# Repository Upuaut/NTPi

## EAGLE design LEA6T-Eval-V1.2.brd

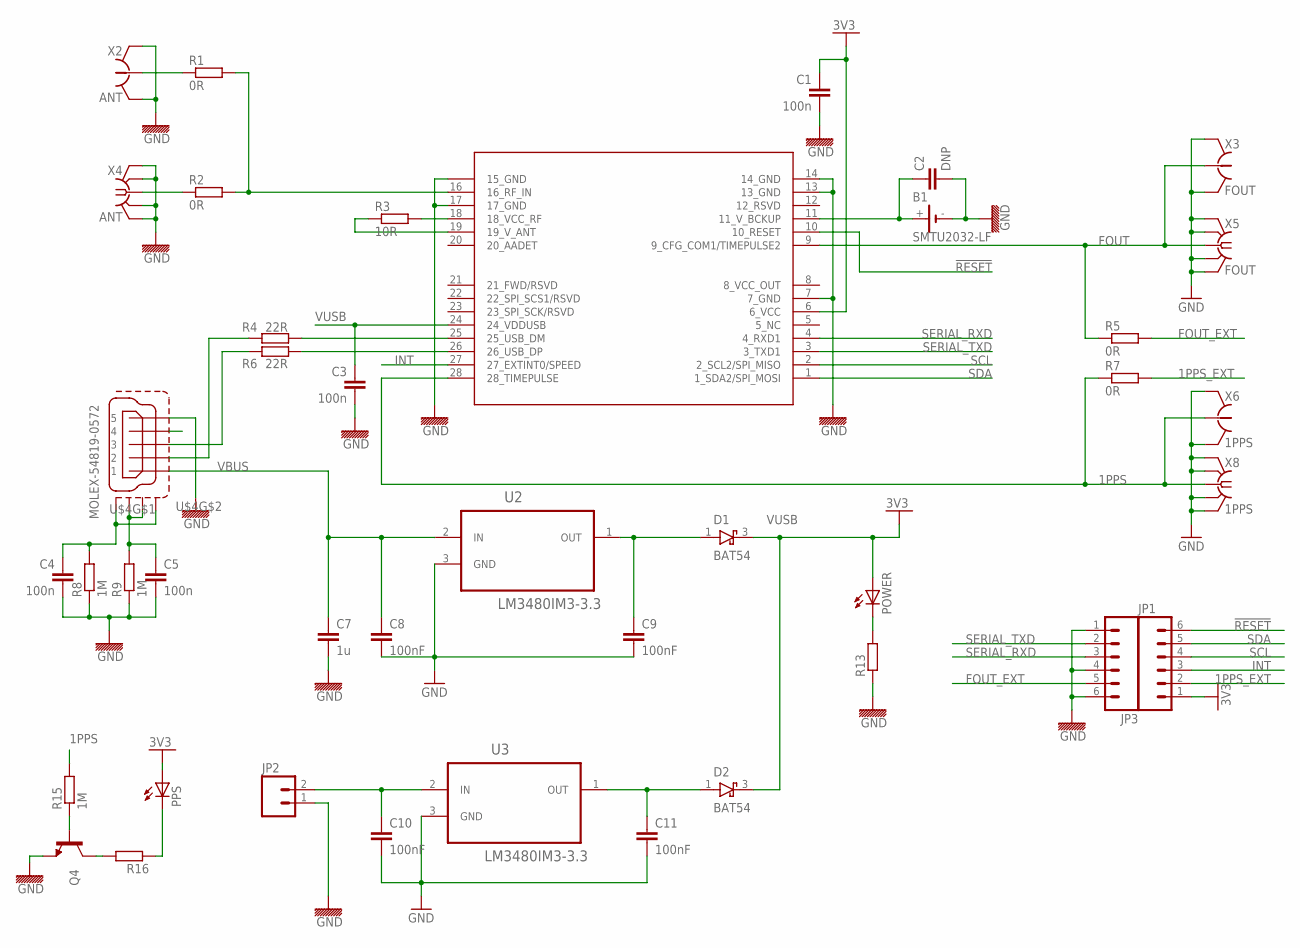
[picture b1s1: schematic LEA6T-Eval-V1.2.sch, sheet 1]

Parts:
B1: SMTU2032-LF; SMTU2032
C1, C3, C4, C5: 100n; 0603
C2: DNP; 0603
C7: 1u; 0603
C8, C9, C10, C11: 100nF; 0603-CAP
D1, D2: BAT54; SOT23
JP1, JP3: M06SIP; 1X06
JP2: M02PTH; 1X02
POWER: LEDSML0603; SML0603
PPS: LEDSML0603; SML0603
Q4: TRANSISTOR_NPNSOT23; SOT23
R1, R2, R5, R7: 0R; 0603
R3: 10R; 0603
R4, R6: 22R; 0603
R8, R9, R15: 1M; 0603
R13, R16: R-EU_0603; 0603
U1: UBLOX_LEA-6; UBLOX_LEA-6T
U2, U3: LM3480IM3-3.3; SOT95P251X112-3N
U$4: MOLEX-54819-0572
X2: ANT; HRS_UFL
X3: FOUT; HRS_UFL
X4: ANT; SMA-F-S-EDGE
X5: FOUT; SMA-F-S-EDGE
X6: 1PPS; HRS_UFL
X8: 1PPS; SMA-F-S-EDGE

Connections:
1PPS: R7.1, R15.2, U1.28 (28_TIMEPULSE), X6.SIG (1), X8.C (1)
1PPS_EXT: JP1.2, R7.2; also elsewhere on the board
3V3: C1.1, D1.3 (C), D2.3 (C), JP1.1, POWER.A, PPS.A, U1.6 (6_VCC); also elsewhere on the board
!RESET: JP1.6, U1.10 (10_RESET)
FOUT: R5.1, U1.9 (9_CFG_COM1/TIMEPULSE2), X3.SIG (1), X5.C (1)
FOUT_EXT: JP3.5, R5.2; also elsewhere on the board
GND: B1.-, C1.2, C2.2, C3.2, C4.2, C5.2, C7.2, C8.2, C9.2, C10.2, C11.2, JP2.1, JP3.1, JP3.4, JP3.6, Q4.2 (E), R8.1, R9.1, R13.1, U1.7 (7_GND), U1.13 (13_GND), U1.14 (14_GND), U1.15 (15_GND), U1.17 (17_GND), U2.3 (GND), U3.3 (GND), U$4.5, X2.GND@1 (GND), X2.GND@2 (GND), X3.GND@1 (GND), X3.GND@2 (GND), X4.BG1 (GND), X4.BG2 (GND), X4.TG1 (GND), X4.TG2 (GND), X5.BG1 (GND), X5.BG2 (GND), X5.TG1 (GND), X5.TG2 (GND), X6.GND@1 (GND), X6.GND@2 (GND), X8.BG1 (GND), X8.BG2 (GND), X8.TG1 (GND), X8.TG2 (GND); also elsewhere on the board
INT: JP1.3, U1.27 (27_EXTINT0/SPEED)
unnamed: R2.1, X4.C (1)
unnamed: C4.1, R8.2, U$4.M1 (S1), U$4.M4 (S4)
unnamed: R4.2, U1.25 (25_USB_DM)
unnamed: R6.2, U1.26 (26_USB_DP)
unnamed: R3.2, U1.18 (18_VCC_RF)
unnamed: R3.1, U1.19 (19_V_ANT)
unnamed: C10.1, JP2.2, U3.2 (IN)
unnamed: C11.1, D2.1 (A), U3.1 (OUT)
unnamed: R6.1, U$4.3
unnamed: R4.1, U$4.2
unnamed: B1.+, C2.1, U1.11 (11_V_BCKUP)
unnamed: R1.1, X2.SIG (1)
unnamed: R1.2, R2.2, U1.16 (16_RF_IN)
unnamed: C5.1, R9.2, U$4.M2 (S2), U$4.M3 (S3)
unnamed: POWER.C, R13.2
unnamed: Q4.3 (C), R16.2
unnamed: Q4.1 (B), R15.1
unnamed: PPS.C, R16.1
SCL: JP1.4, U1.2 (2_SCL2/SPI_MISO); also elsewhere on the board
SDA: JP1.5, U1.1 (1_SDA2/SPI_MOSI); also elsewhere on the board
SERIAL_RXD: JP3.3, U1.4 (4_RXD1); also elsewhere on the board
SERIAL_TXD: JP3.2, U1.3 (3_TXD1); also elsewhere on the board
VBUS: C7.1, C8.1, U2.2 (IN), U$4.1
VUSB: C3.1, C9.1, D1.1 (A), U1.24 (24_VDDUSB), U2.1 (OUT)

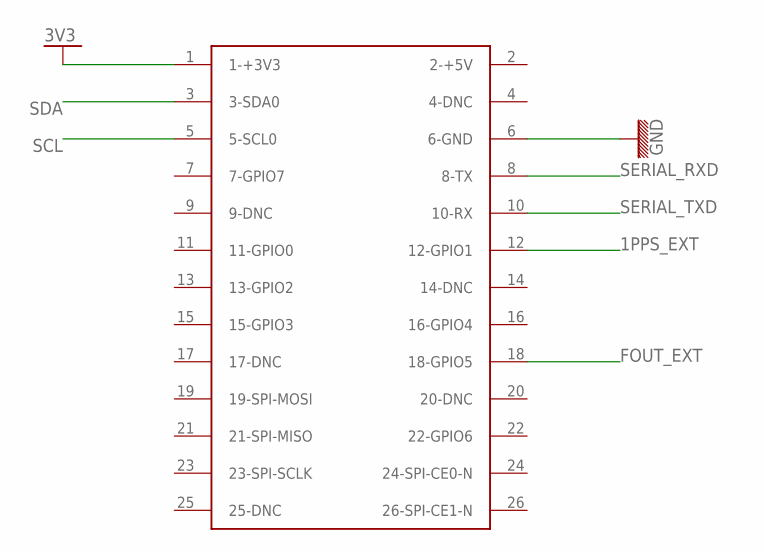
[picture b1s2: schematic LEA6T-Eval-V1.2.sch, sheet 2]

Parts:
U$30: RASPBERRY-PINOCRAP; RASPBERRY-PI_NOCONNS

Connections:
1PPS_EXT: U$30.12 (12-GPIO1); also elsewhere on the board
3V3: U$30.1 (1-+3V3); also elsewhere on the board
FOUT_EXT: U$30.18 (18-GPIO5); also elsewhere on the board
GND: U$30.6 (6-GND); also elsewhere on the board
SCL: U$30.5 (5-SCL0); also elsewhere on the board
SDA: U$30.3 (3-SDA0); also elsewhere on the board
SERIAL_RXD: U$30.8 (8-TX); also elsewhere on the board
SERIAL_TXD: U$30.10 (10-RX); also elsewhere on the board

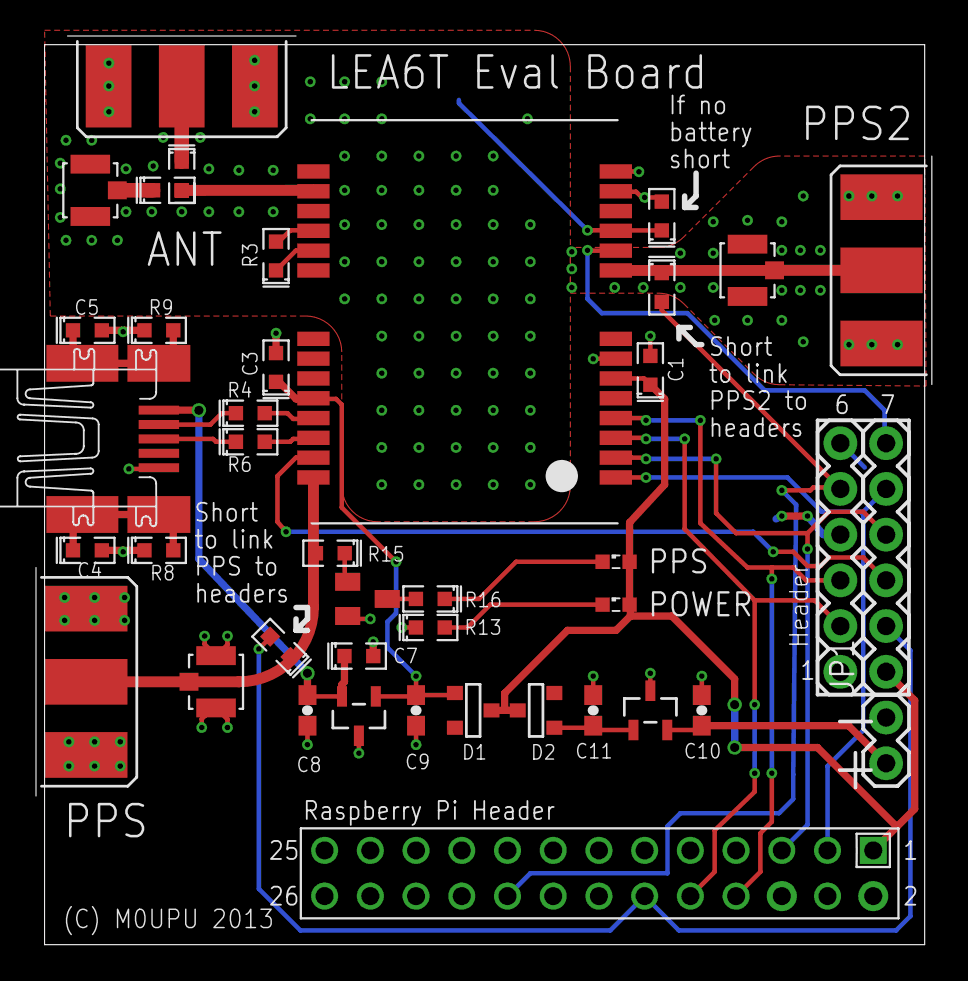
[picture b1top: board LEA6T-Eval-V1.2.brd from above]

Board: 2 copper layers, 48.9 x 50.0 mm, 42 parts (1 on the bottom side), 32 nets.

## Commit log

2013-08-09 Added Page 2 of PDF

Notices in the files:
parts and their libraries:
SparkFun: Licensing: CC v3.0 Share-Alike You are welcome to use this library for commercial purposes.
